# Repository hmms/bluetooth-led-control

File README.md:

bluetooth-led-control
=====================

A Arduino Powered RGB LED lighting Controller with a bluetooth interface. Change the color and the pattern displayed on the RGB LEDs using your bluetooth enabled smartphone or computer

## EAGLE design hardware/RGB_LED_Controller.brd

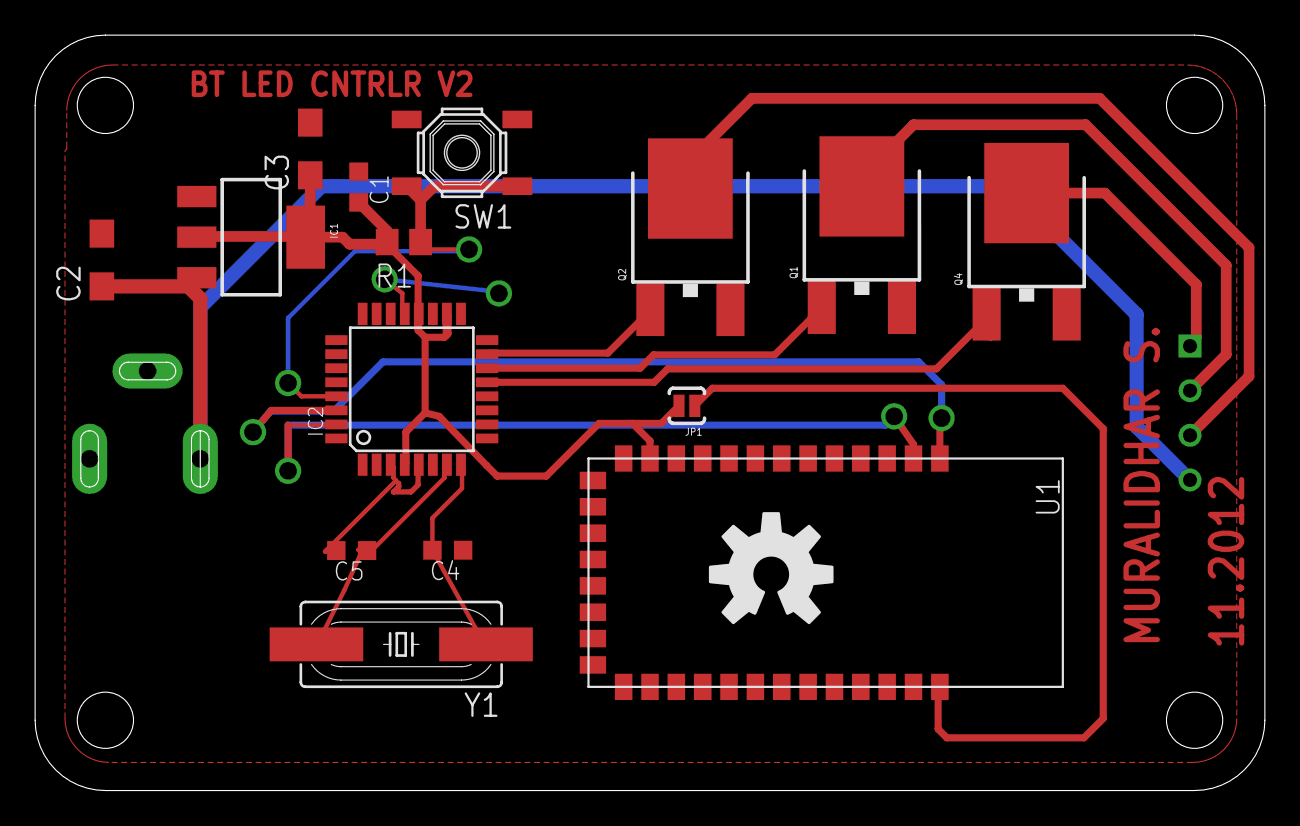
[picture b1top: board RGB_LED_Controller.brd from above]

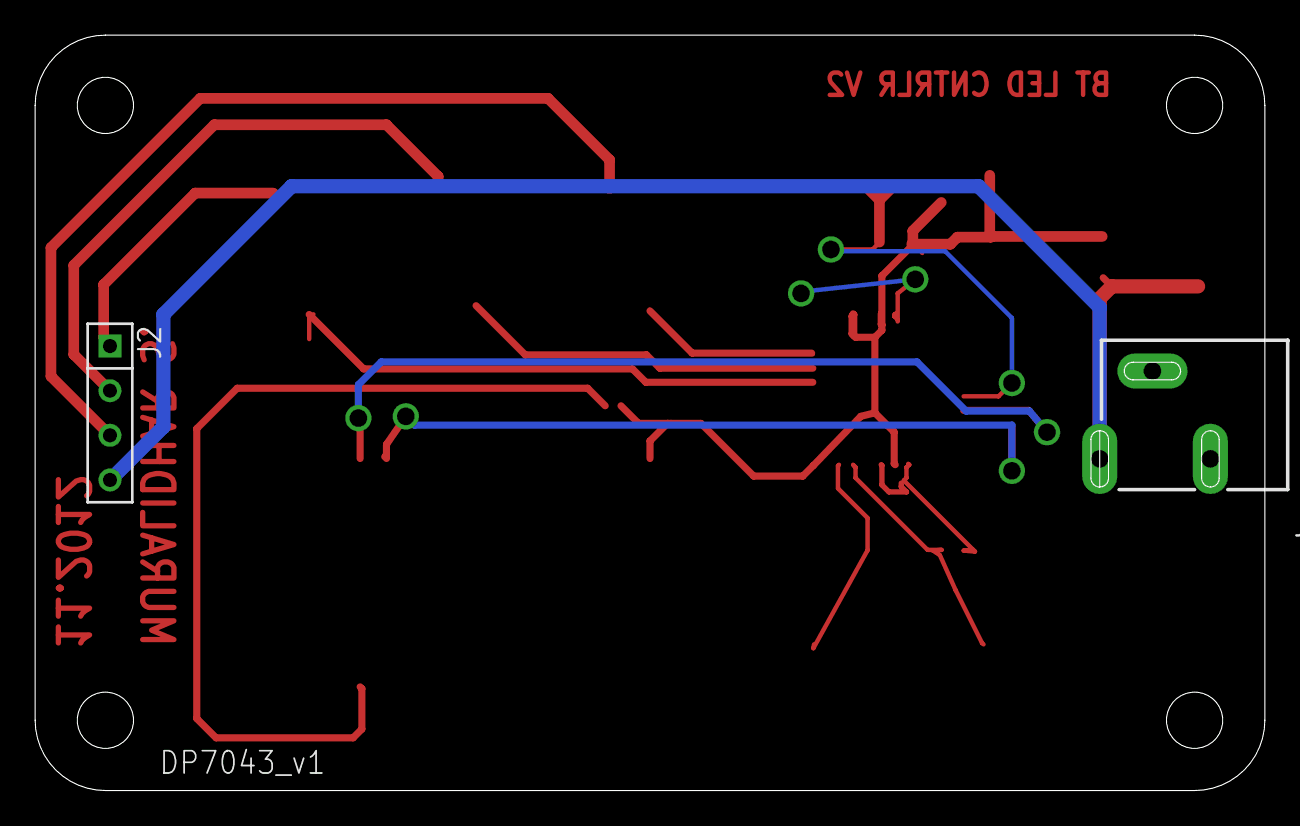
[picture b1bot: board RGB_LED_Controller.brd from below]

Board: 2 copper layers, 70.0 x 43.0 mm, 19 parts (2 on the bottom side), 15 nets.

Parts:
C1, C4, C5: C0603K
C2, C3: 10uF; SMC_A
E$1: OSHW-LOGO-L
IC1: SOT223
IC2: MEGA8-AI; TQFP32-08
J1: POWER_JACKSLT; POWER_JACK_SLOT
J2: CON_HEADER_1X04; M1X4
JP1: SJ_2S-NO
Q1, Q2, Q4: MOSFET-NCHANNELFDD8580; DPAK
R1: R0805
SW1: SW_TACT_SMALL
U1: HC_05; BLUETOOTH_SMD
U$1: DP7043_V1
Y1: HC49UP

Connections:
12V: C2.+, IC1.3, J1.PWR, J2.4
+3V3: C1.2, C3.+, IC1.2, IC1.4, IC2.4, IC2.18, IC2.20, JP1.2, R1.2, U1.12
GND: C1.1, C2.-, C3.-, C4.1, C5.2, IC1.1, IC2.3, IC2.5, IC2.21, J1.GND@1, J1.GND@2, Q1.3, Q2.3, Q4.3, SW1.3, SW1.4, U1.13, U1.21, U1.22
unnamed: IC2.13, Q4.1
unnamed: IC2.14, Q1.1
unnamed: IC2.15, Q2.1
unnamed: IC2.29, R1.1, SW1.1, SW1.2
unnamed: C5.1, IC2.7, Y1.2
unnamed: J2.1, Q4.4
unnamed: J2.2, Q1.4
unnamed: J2.3, Q2.4
unnamed: C4.2, IC2.8, Y1.1
unnamed: JP1.1, U1.34
RX: IC2.31, U1.2
TX: IC2.30, U1.1

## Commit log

2012-10-06 First Commit With all working Code and Design Files
2012-10-11 Mobile Phone Gui moved into symbainS60 folder
2012-10-30 DP 6037 pcb form factor same as bus pirate. All SMD design
2012-10-31 some routing done. PCB modified to 7043
2012-10-31 routing done.Optimize before printing
2012-11-01 PCB labelled
2012-11-02 OSHW logo added.Some track optimisations
2012-11-02 GND plane Isolate increased to prevent issues during toner transfer
2012-11-02 schematic inconsistency with board issue resolved
2012-11-02 barrel jack was connected in reverse. corrected now.
2012-11-02 stray track removed
2012-11-06 work in progress android app added to repo
2012-11-09 Bluetooth module changed from aubtm-20 to more easily available HC-05. Footprints for through hole parts mirrored.
2012-11-09 rev 3 PCB. Printout taken

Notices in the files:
parts and their libraries:
SparkFun: Licensing: CC v3.0 Share-Alike You are welcome to use this library for commercial purposes.
